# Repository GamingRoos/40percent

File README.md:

# THIS IS A WORK IN PROGRESS

I'm designing a 40% keyboard just for the fun of it and to learn how to make everything from scratch.  

There should be every required file in Git Repository for you to build your own, I'll also include the bill of materials for both KiCad/JLCPCB and also DigiKey if you wish to solder it all by hand.  

Here a few of the features of the board:

> - USB-C Support (USB2.0 for easy compatibility)
> - ATMEGA32U4 Microcontroller (Easily available and ready firmware support through QMK)
> - Live keymapping through QMK/VIAL
> - Gasket Mounting (Gummy O-Ring)
> - MOSTLY screwless Design (Excluding the four to mount the daughterboard)    
I'll think of more later    

What does the board conceptually look like?  

PgDn and PgUp will be Layer Keys  
Cool!  

> #### Bill of Materials:  
>
> ##### Main Keyboard
>
> - 1 ATMEGA32U4-AUR [DigiKey](https://www.digikey.com.au/en/products/detail/microchip-technology/ATMEGA32U4-AUR/2238241)
> - 1 FA238 16.0000MB-C3 [DigiKey](https://www.digikey.com.au/en/products/detail/epson/FA-238-16-0000MB-C3/2403378)
> - 2 22pf Ceramic Capacitor 50v (0805) [DigiKey](https://www.digikey.com.au/en/products/detail/kemet/C0805C220J5GACTU/411112)
> - 1 1uf Ceramic Capacitor 16v (0805) [DigiKey](https://www.digikey.com.au/en/products/detail/yageo/CC0805KKX7R7BB105/2103103)
> - 1 4.7uf Ceramic Capacitor 25v (0805) [DigiKey](https://www.digikey.com.au/en/products/detail/murata-electronics/GRM219R61E475KA73D/4905426)
> - 2 10K Resistor 5% 1/8W(0805) [DigiKey](https://www.digikey.com.au/en/products/detail/stackpole-electronics-inc/RMCF0805JT10K0/1757762)
> - 1 TL3342F160QG/TR Switch [DigiKey](https://www.digikey.com.au/en/products/detail/e-switch/TL3342F160QG-TR/379003)    
> - 2 SM04B-SRSS-TB JST SH1.0 4Pin Connector [DigiKey](https://www.digikey.com.au/en/products/detail/jst-sales-america-inc/SM04B-SRSS-TB/926710)
> - 1 JST SH1.0 Male/Male Cable (Size not known just yet, also to connect both PCBs)
> - 40 1N4148W/SOD-123 Diodes (0603) [DigiKey](https://www.digikey.com.au/en/products/detail/smc-diode-solutions/1N4148W/6022450)
> - 1 Printed 40percent Case
> - 40 Gateron Hotswap Sockets (Can't find on Digikey, AliExpress?) 
> - 40 MX Compatible Switches (Outemu might not work in the sockets)
> - 1 Suitable Keycap Set
> - 3 2u Plate Mount Stabiliser
> - 1 6.25u Plate Mount Stabiliser
> - 4 8mm Rubber Bump-ons for the feet
> - This MIGHT be a working O-Ring size? I'll have to find out when I make this. [oリング](https://xn--o-7eu7hjb.com/?pid=81334721)
> ##### USB-C Daughter Board
> - 1 USB4105-GF-A-060 USB-C 16pin [DigiKey](https://www.digikey.com.au/en/products/detail/gct/USB4105-GF-A-060/14559036)
> - 2 5.1k Resistor 5% 1/8W (0805) [DigiKey](https://www.digikey.com.au/en/products/detail/yageo/RC0805JR-075K1L/728338)
> - 4 M2 4mm Bolts (Screw straight into posts, if you for some reason chose to mill the case, tap it out... it's at 1.6mm ID)
> - One of the JST connectors from above
> - 1 USB-C to USB-C\A cable
> ### I'd recommend ordering a few more than you need at minimum, just incase you fuck it up. Better safe than sorry. Also, cut down on shipping cost :) Plus 5 PCB minimum from JLCPCB, five chances?

# That's pretty much it so far!

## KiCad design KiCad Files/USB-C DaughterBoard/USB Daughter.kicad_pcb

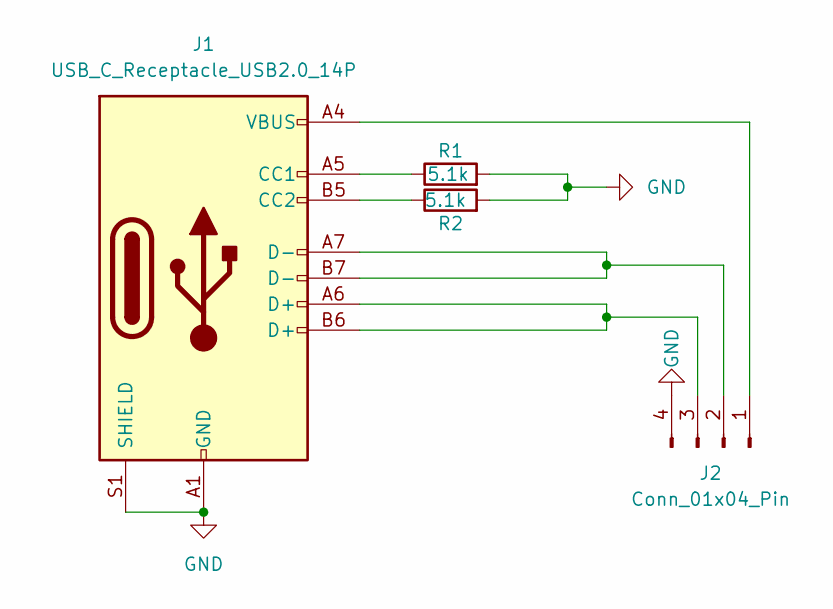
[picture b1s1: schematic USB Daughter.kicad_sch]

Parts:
J1: USB_C_Receptacle_USB2.0_14P; USB_C_Receptacle_GCT_USB4105-xx-A_16P_TopMnt_Horizontal
J2: Conn_01x04_Pin; JST_SH_BM04B-SRSS-TB_1x04-1MP_P1.00mm_Vertical
R1, R2: 5.1k; C_0805_2012Metric_Pad1.18x1.45mm_HandSolder

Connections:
GND: J1.A1 (GND), J1.A12 (GND), J1.B1 (GND), J1.B12 (GND), J1.S1 (SHIELD), J2.4, R1.2, R2.2
unnamed: J1.A5 (CC1), R1.1
unnamed: J1.B5 (CC2), R2.1
unnamed: J1.A4 (VBUS), J1.A9 (VBUS), J1.B4 (VBUS), J1.B9 (VBUS), J2.1
unnamed: J1.A7 (D-), J1.B7 (D-), J2.2
unnamed: J1.A6 (D+), J1.B6 (D+), J2.3

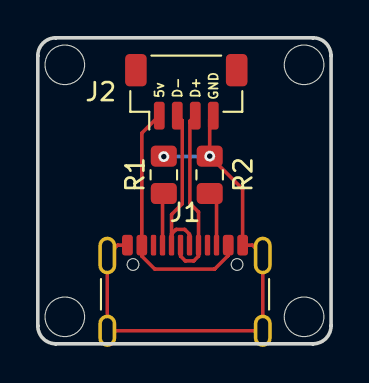
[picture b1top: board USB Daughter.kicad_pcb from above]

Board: 2 copper layers, 16.3 x 17.0 mm, 4 parts (0 on the bottom side), 6 nets.

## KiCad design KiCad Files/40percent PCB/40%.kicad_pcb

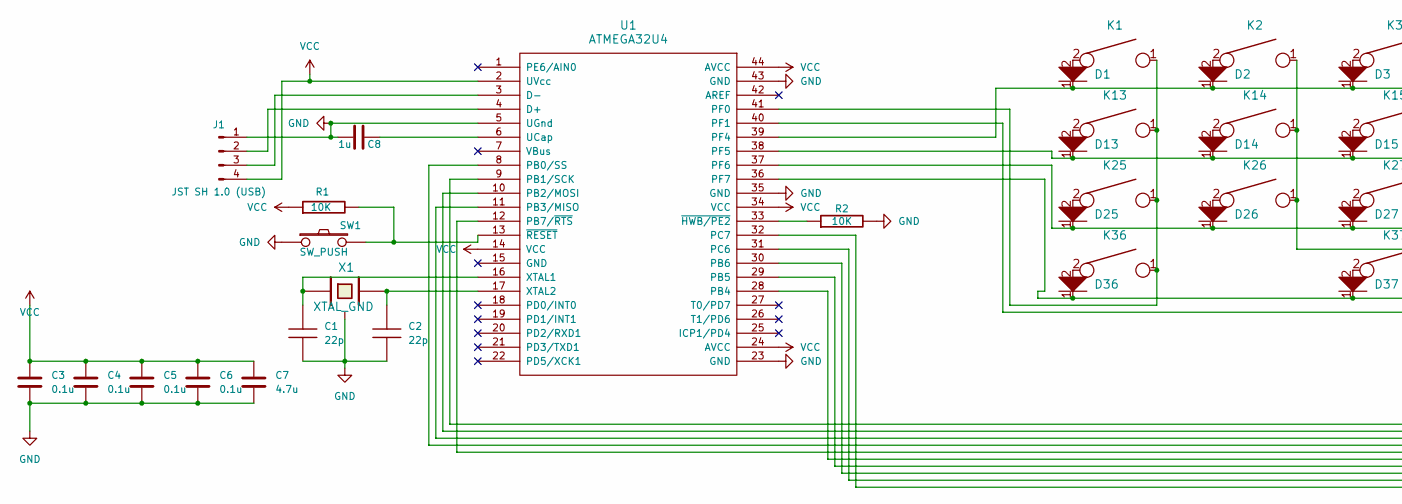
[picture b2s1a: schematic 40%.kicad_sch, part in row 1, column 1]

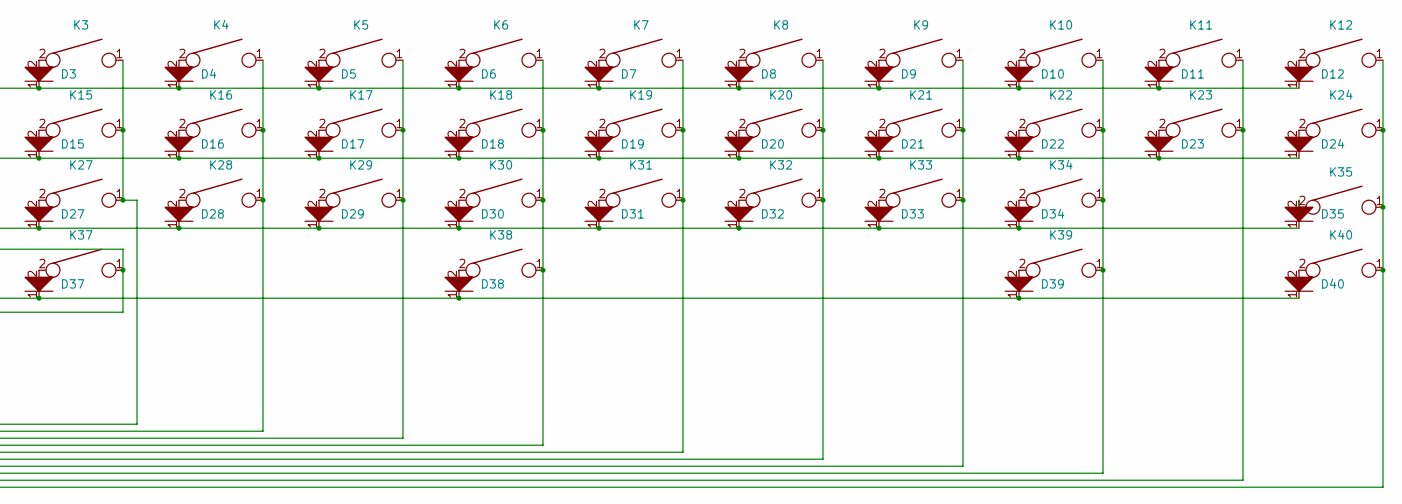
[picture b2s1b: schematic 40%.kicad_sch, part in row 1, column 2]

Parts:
C1, C2: 22p; C_0805_2012Metric
C3, C4, C5, C6: 0.1u; C_0805_2012Metric
C7: 4.7u; C_0805_2012Metric
C8: 1u; C_0805_2012Metric
D1, D2, D3, D4, D5, D6, D7, D8, D9, D10, D11, D12, D13, D14, D15, D16, D17, D18, D19, D20, D21, D22, D23, D24, D25, D26, D27, D28, D29, D30, D31, D32, D33, D34, D35, D36, D37, D38, D39, D40: D; D_SOD-123
J1: JST SH 1.0 (USB); JST_SH_BM04B-SRSS-TB_1x04-1MP_P1.00mm_Vertical
K1, K2, K3, K4, K5, K6, K7, K8, K9, K10, K11, K12, K13, K14, K15, K16, K17, K18, K19, K20, K21, K22, K23, K24, K25, K26, K27, K28, K29, K30, K31, K32, K33, K34, K35, K36, K37, K38, K39, K40: KEYSW; SW_Hotswap_Kailh_MX
R1, R2: 10K; R_0805_2012Metric_Pad1.20x1.40mm_HandSolder
SW1: SW_PUSH; SW_SPST_TL3342
U1: ATMEGA32U4; TQFP-44_10x10mm_P0.8mm
X1: XTAL_GND; Crystal_SMD_SeikoEpson_FA238-4pin_3.2x2.5mm_HandSoldering

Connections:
unnamed: D1.2, K1.2
unnamed: D2.2, K2.2
unnamed: D3.2, K3.2
unnamed: D4.2, K4.2
unnamed: D5.2, K5.2
unnamed: D6.2, K6.2
unnamed: D7.2, K7.2
unnamed: D8.2, K8.2
unnamed: D9.2, K9.2
unnamed: D10.2, K10.2
unnamed: D11.2, K11.2
unnamed: D12.2, K12.2
unnamed: D13.2, K13.2
unnamed: D14.2, K14.2
unnamed: D15.2, K15.2
unnamed: D16.2, K16.2
unnamed: D17.2, K17.2
unnamed: D18.2, K18.2
unnamed: D19.2, K19.2
unnamed: D20.2, K20.2
unnamed: D21.2, K21.2
unnamed: D22.2, K22.2
unnamed: D23.2, K23.2
unnamed: D24.2, K24.2
unnamed: D25.2, K25.2
unnamed: D26.2, K26.2
unnamed: D27.2, K27.2
unnamed: D28.2, K28.2
unnamed: D29.2, K29.2
unnamed: D30.2, K30.2
unnamed: D31.2, K31.2
unnamed: D32.2, K32.2
unnamed: D33.2, K33.2
unnamed: D34.2, K34.2
unnamed: D35.2, K35.2
unnamed: D36.2, K36.2
unnamed: D37.2, K37.2
unnamed: D38.2, K38.2
unnamed: D39.2, K39.2
unnamed: D40.2, K40.2
unnamed: J1.2 (Pin_3), U1.4 (D+)
unnamed: J1.3 (Pin_2), U1.3 (D-)
unnamed: K6.1, K18.1, K30.1, K38.1, U1.8 (PB0/SS)
unnamed: K3.1, K15.1, K27.1, U1.9 (PB1/SCK)
unnamed: K4.1, K16.1, K28.1, U1.10 (PB2/MOSI)
unnamed: K5.1, K17.1, K29.1, U1.11 (PB3/MISO)
unnamed: K8.1, K20.1, K32.1, U1.28 (PB4)
unnamed: K9.1, K21.1, K33.1, U1.29 (PB5)
unnamed: K10.1, K22.1, K34.1, K39.1, U1.30 (PB6)
unnamed: K7.1, K19.1, K31.1, U1.12 (PB7/~RTS)
unnamed: K11.1, K23.1, U1.31 (PC6)
unnamed: K12.1, K24.1, K35.1, K40.1, U1.32 (PC7)
unnamed: K1.1, K13.1, K25.1, K36.1, U1.41 (PF0)
unnamed: K2.1, K14.1, K26.1, K37.1, U1.40 (PF1)
unnamed: D1.1, D2.1, D3.1, D4.1, D5.1, D6.1, D7.1, D8.1, D9.1, D10.1, D11.1, D12.1, U1.39 (PF4)
unnamed: D13.1, D14.1, D15.1, D16.1, D17.1, D18.1, D19.1, D20.1, D21.1, D22.1, D23.1, D24.1, U1.38 (PF5)
unnamed: D25.1, D26.1, D27.1, D28.1, D29.1, D30.1, D31.1, D32.1, D33.1, D34.1, D35.1, U1.37 (PF6)
unnamed: D36.1, D37.1, D38.1, D39.1, D40.1, U1.36 (PF7)
unnamed: C8.1, U1.6 (UCap)
unnamed: C1.1, U1.16 (XTAL1), X1.1
unnamed: R2.1, U1.33 (~HWB/PE2)
unnamed: R1.2, SW1.2, U1.13 (~RESET)

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
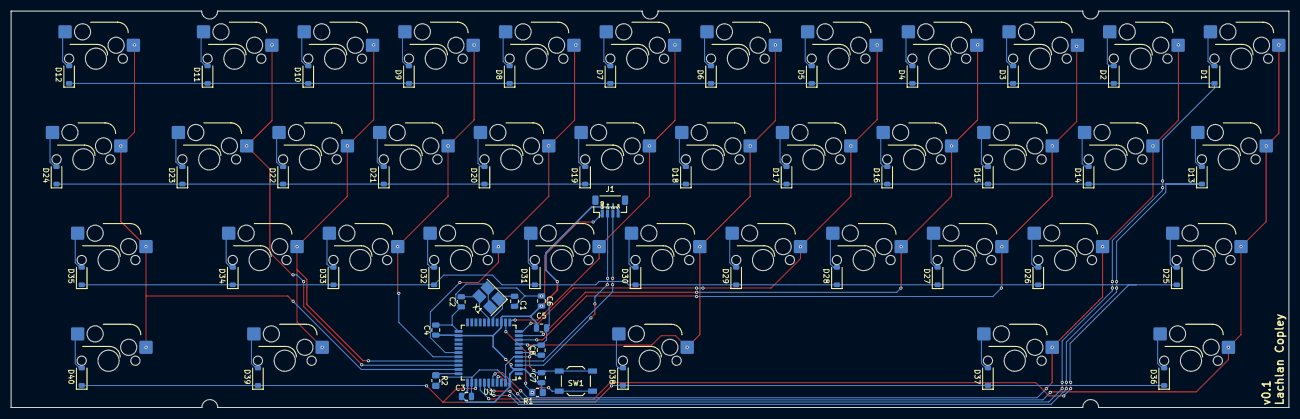
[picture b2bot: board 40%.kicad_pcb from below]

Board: 2 copper layers, 241.8 x 75.0 mm, 94 parts (54 on the bottom side), 65 nets.

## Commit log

2025-05-07 Cases
2025-05-07 Just added EVERYTHING
